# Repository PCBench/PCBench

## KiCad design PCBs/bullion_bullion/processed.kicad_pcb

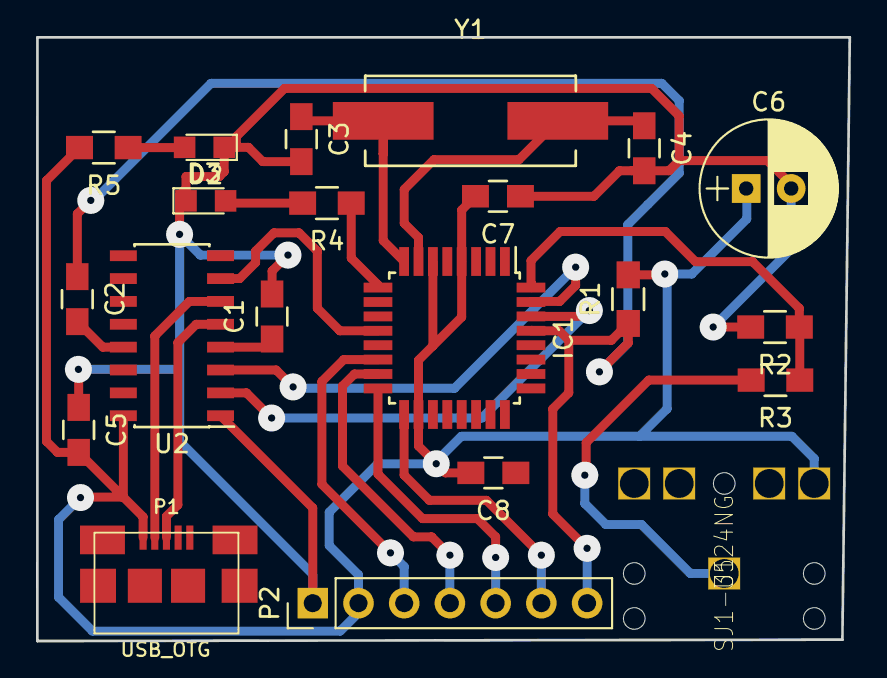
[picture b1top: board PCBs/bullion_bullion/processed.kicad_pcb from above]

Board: 2 copper layers, 45.1 x 33.5 mm, 21 parts (0 on the bottom side), 21 nets.

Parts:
C1, C2, C5, C7, C8: 0.1u; C_0805_HandSoldering
C3, C4: 22p; C_0805_HandSoldering
C6: 47u; CP_Radial_D7.5mm_P2.50mm
D2: BLUE; LED_0805
D3: RED; LED_0805
IC1: ATMEGA328P-A; TQFP-32_7x7mm_Pitch0.8mm
P1: USB_OTG; MICRO-B_USB
P2: CONN_01X07; Pin_Header_Straight_1x07_Pitch2.54mm
R1: 10k; R_0805_HandSoldering
R2: 2.2k; R_0805_HandSoldering
R3: 220; R_0805_HandSoldering
R4: 82; R_0805_HandSoldering
R5: 4.7k; R_0805_HandSoldering
U1: SJ1-3524NG; PIN-4
U2: CH340G; SOIC-16_3.9x9.9mm_Pitch1.27mm
Y1: Crystal; Crystal_HC49-SD_SMD

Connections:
+5V: C5.2, C6.1, C7.2, C8.2, IC1.4, IC1.6, IC1.18, P1.1, P2.2, R1.2, R5.2, U1.2, U2.16
CLKOUT: IC1.12, U2.7
DTR: C2.2, U2.13
GND: C1.2, C3.2, C4.2, C5.1, C6.2, C7.1, D2.1, D3.1, P2.1, R2.2, U2.1
MM_TXD: IC1.32, R2.1, R3.1
unnamed: C1.1, U2.4
unnamed: C2.1, IC1.29, P2.7, R1.1
unnamed: C3.1, IC1.8, Y1.1
unnamed: C4.1, IC1.7, Y1.2
unnamed: D2.2, R4.2
unnamed: D3.2, R5.1
unnamed: IC1.9, R4.1
unnamed: IC1.14, P2.3
unnamed: IC1.15, P2.4
unnamed: IC1.16, P2.5
unnamed: IC1.17, P2.6
unnamed: P1.2, U2.6
unnamed: P1.3, U2.5
unnamed: R3.2, U1.1
RXD: IC1.30, U2.2
TXD: IC1.31, U2.3

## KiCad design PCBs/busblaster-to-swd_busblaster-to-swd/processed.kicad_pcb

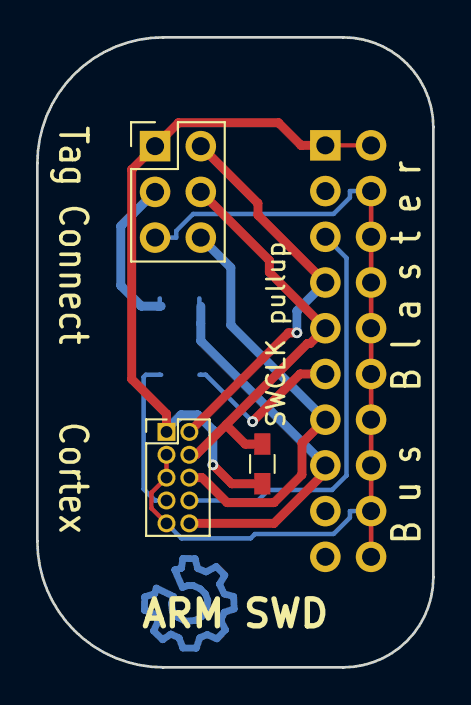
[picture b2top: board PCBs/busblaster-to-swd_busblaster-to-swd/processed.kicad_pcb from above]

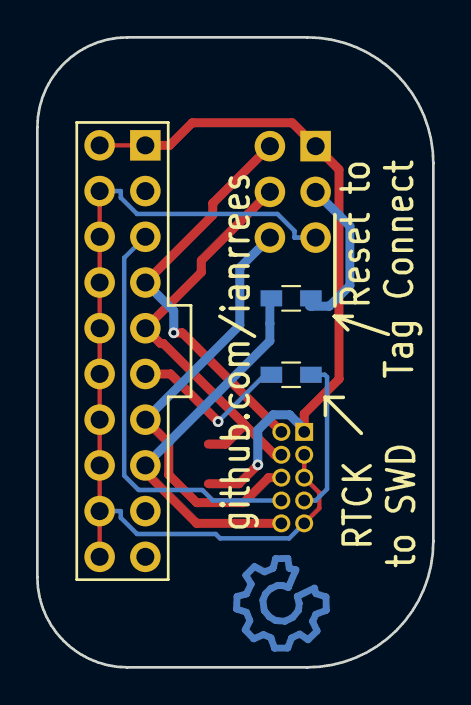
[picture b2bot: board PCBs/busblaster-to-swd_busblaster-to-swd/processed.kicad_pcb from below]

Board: 2 copper layers, 22.0 x 35.0 mm, 6 parts (2 on the bottom side), 10 nets.

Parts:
J101: CONN_02X10; Pin_Header_Straight_2x10_Pitch2.54mm
J102: Tag Connect; Pin_Header_Straight_2x03_Pitch2.54mm
J103: CONN_02X05; Pin_Header_Straight_2x05_Pitch1.27mm
JP101, JP102: Jumper_NC_Small; R_0603_HandSoldering
R101: 1k; R_0603_HandSoldering

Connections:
/GND: J101.4, J101.6, J101.8, J101.10, J101.12, J101.14, J101.16, J101.18, J101.20, J102.5, J103.3, J103.5, J103.9
/RTCK: J103.7, JP102.2
/SWO/TDO: J101.13, J102.6, J103.6
/TCK/SWCLK: J101.9, J102.4, J103.4, R101.2
/TDI: J101.5, J103.8
/TMS/SWDIO: J101.7, J102.2, J103.2
/Vtarget: J101.1, J101.2, J102.1, J103.1, R101.1
/~Reset: J102.3, JP101.1
unnamed: J101.11, JP102.1
unnamed: J101.15, J103.10, JP101.2

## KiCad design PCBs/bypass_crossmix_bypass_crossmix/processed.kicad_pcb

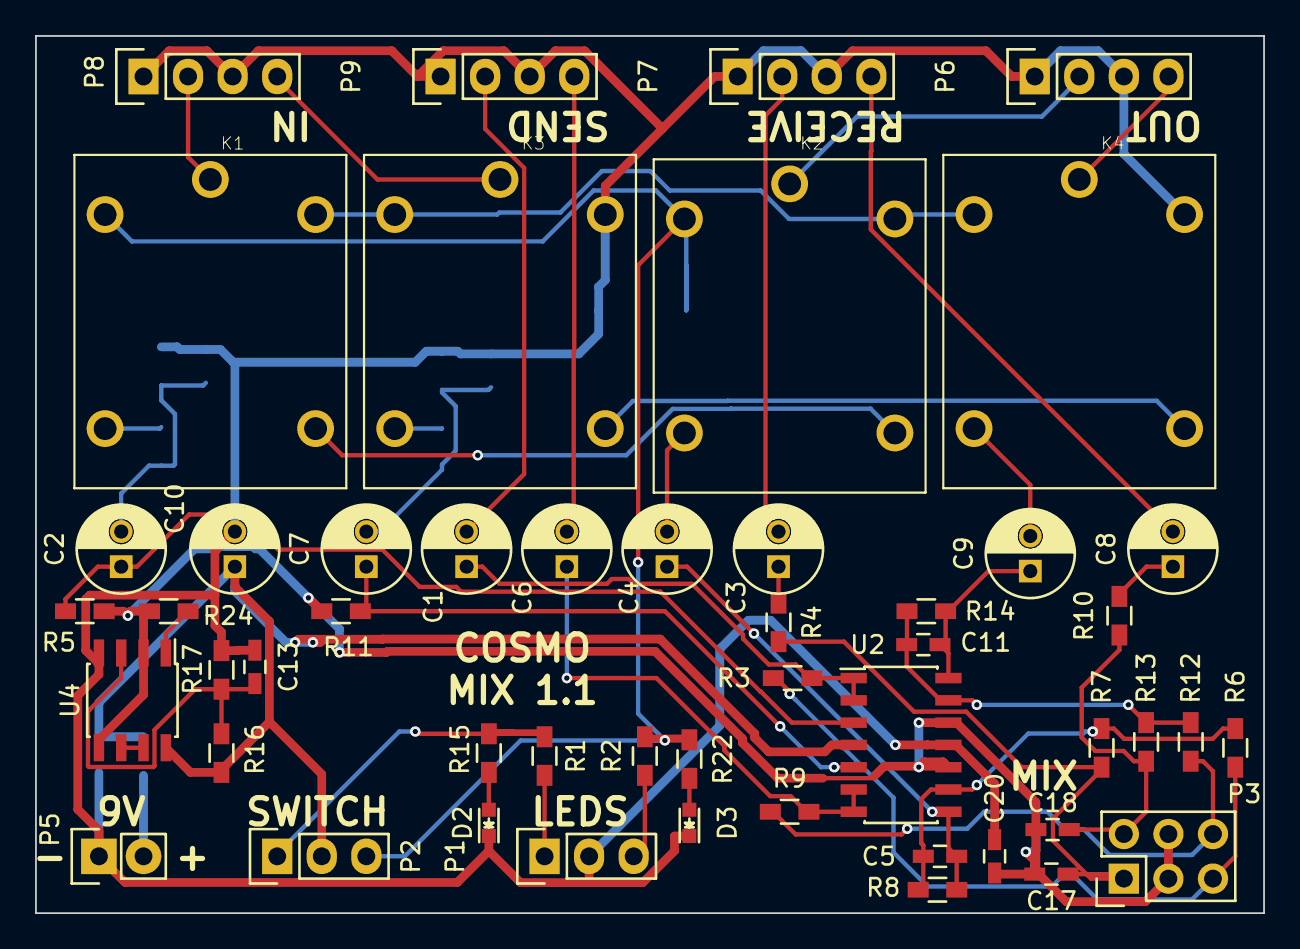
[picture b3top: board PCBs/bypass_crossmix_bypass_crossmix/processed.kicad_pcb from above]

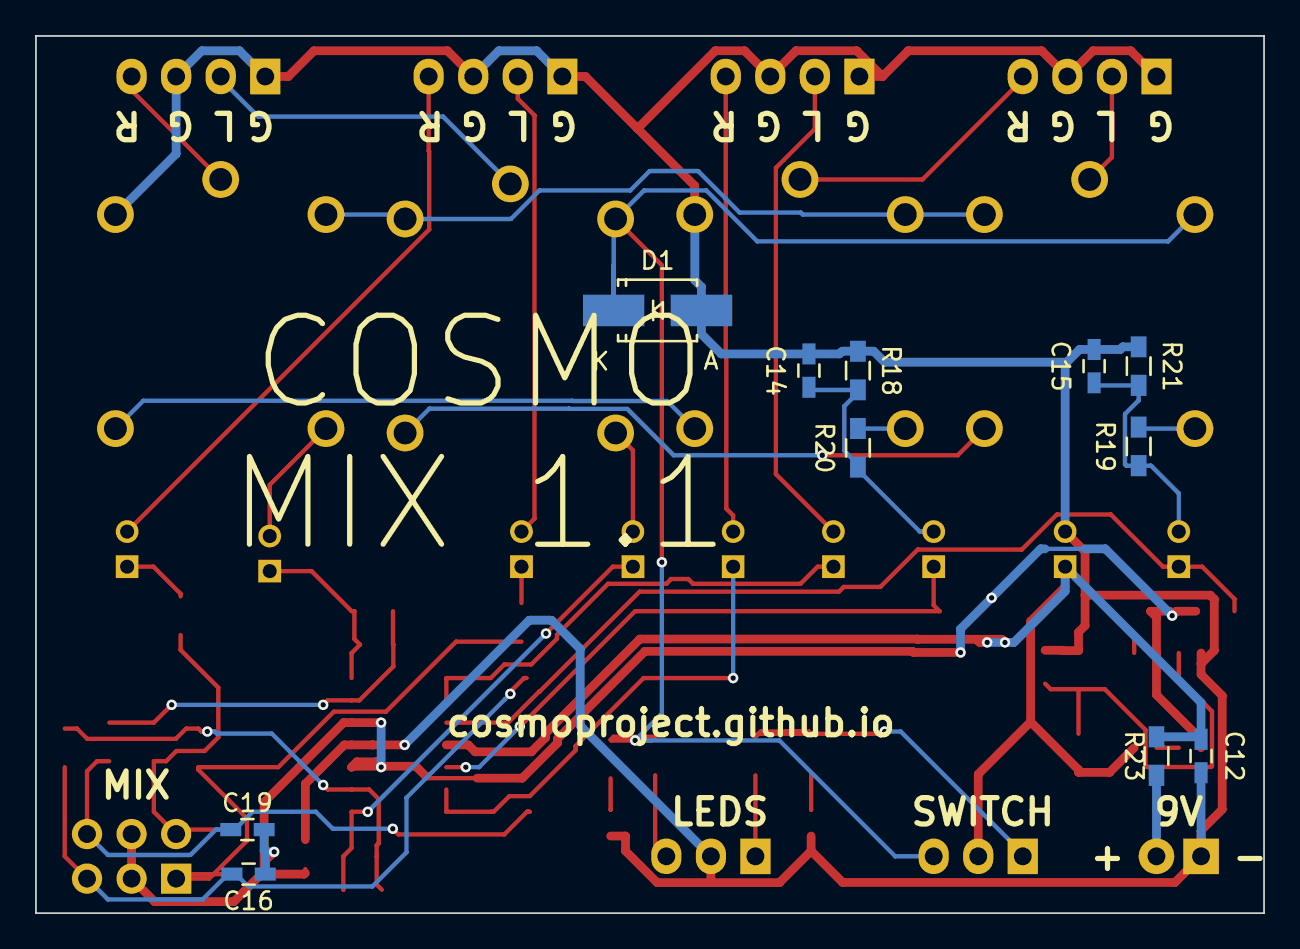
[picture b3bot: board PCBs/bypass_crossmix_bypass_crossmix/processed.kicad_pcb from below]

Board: 2 copper layers, 70.0 x 50.0 mm, 61 parts (11 on the bottom side), 44 nets.

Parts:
C1, C2, C3, C4, C6, C7, C8, C9, C10: 100u; C_Radial_D5_L11_P2
C5, C11: C; C_0603_HandSoldering
C12, C13, C20: 100n; C_0603_HandSoldering
C14, C15: 10n; C_0603_HandSoldering
C16, C17, C18, C19: 100p; C_0603_HandSoldering
D1: D; SMA_Handsoldering
D2: RED; LED-0603
D3: GREEN; LED-0603
K1, K2, K3, K4: RELAY-HLS8L-DC5V-S-C(5P-19X15MM); REY5-19.0X15.0X15.0MM
P1: STATUS LED; Pin_Header_Straight_1x03
P2: SWITCH; Pin_Header_Straight_1x03
P3: DRYWET; Pin_Header_Straight_2x03
P5: 9V; Pin_Header_Straight_1x02
P6: OUT; Pin_Header_Straight_1x04
P7: RECEIVE; Pin_Header_Straight_1x04
P8: IN; Pin_Header_Straight_1x04
P9: SEND; Pin_Header_Straight_1x04
R1, R15: 180; R_0603_HandSoldering
R2, R22: 150; R_0603_HandSoldering
R3, R4, R6, R7, R9, R10, R12, R13, R16, R17: 47k; R_0603_HandSoldering
R5, R11, R18, R21: 1M; R_0603_HandSoldering
R8, R14: 100k; R_0603_HandSoldering
R19, R20: 470; R_0603_HandSoldering
R23, R24: 12; R_0603_HandSoldering
U2: TL074; SOIC-14_3.9x8.7mm_Pitch1.27mm
U4: LM358; SOIC-8_3.9x4.9mm_Pitch1.27mm

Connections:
+5V: C10.1, C12.1, P2.2, R16.1, R23.1, U2.4, U4.8
-5V: C10.2, C12.2, C13.1, C14.2, C15.2, C20.2, D1.2, D2.1, D3.1, K3.3, K4.3, P1.2, P5.1, P6.1, P6.3, P7.1, P7.3, P8.1, P8.3, P9.1, P9.3, R17.2, R18.1, R21.1, U2.11, U4.4
/in_left: K1.1, P8.2
/in_right: K3.1, P8.4
/out_left: K2.1, P6.2
/out_right: K4.1, P6.4
/receive_left: C3.2, P7.2
/receive_right: C8.2, P7.4
/send_left: C1.2, P9.2
/send_right: C6.2, P9.4
GND: C16.1, C17.2, C18.2, C19.1, C20.1, P3.3, P3.4, R5.2, R11.2, R24.1, U2.10, U2.12, U4.2, U4.5
unnamed: C1.1, R3.2, U2.1, U2.2
unnamed: C2.1, R5.1, U2.3
unnamed: C3.1, R4.1
unnamed: C4.1, C5.2, R8.2, U2.8
unnamed: C4.2, K2.4
unnamed: C5.1, R6.1, R7.1, R8.1, U2.9
unnamed: C6.1, R9.2, U2.6, U2.7
unnamed: C7.1, R11.1, U2.5
unnamed: C8.1, R10.1
unnamed: C9.2, K4.4
unnamed: C11.1, R12.1, R13.1, R14.1, U2.13
unnamed: C9.1, C11.2, R14.2, U2.14
unnamed: C13.2, R16.2, R17.1, U4.3
unnamed: C7.2, C14.1, R18.2, R20.1
unnamed: C2.2, C15.1, R19.1, R21.2
unnamed: C16.2, P3.5, R3.1, R6.2
unnamed: C17.1, P3.1, R4.2, R7.2
unnamed: C18.1, P3.2, R10.2, R13.2
unnamed: C19.2, P3.6, R9.1, R12.2
unnamed: D1.1, K1.2, K2.2, P2.3, R2.2, R22.1
unnamed: D2.2, R15.1
unnamed: D3.2, R22.2
unnamed: K1.3, K2.3, K3.2, K4.2
unnamed: K1.4, R19.2
unnamed: K1.5, K2.5
unnamed: K3.4, R20.2
unnamed: K3.5, K4.5
unnamed: P1.1, R1.1
unnamed: P1.3, R2.1
unnamed: P2.1, R1.2, R15.2
unnamed: P5.2, R23.2
unnamed: R24.2, U4.1
unnamed: U4.6, U4.7

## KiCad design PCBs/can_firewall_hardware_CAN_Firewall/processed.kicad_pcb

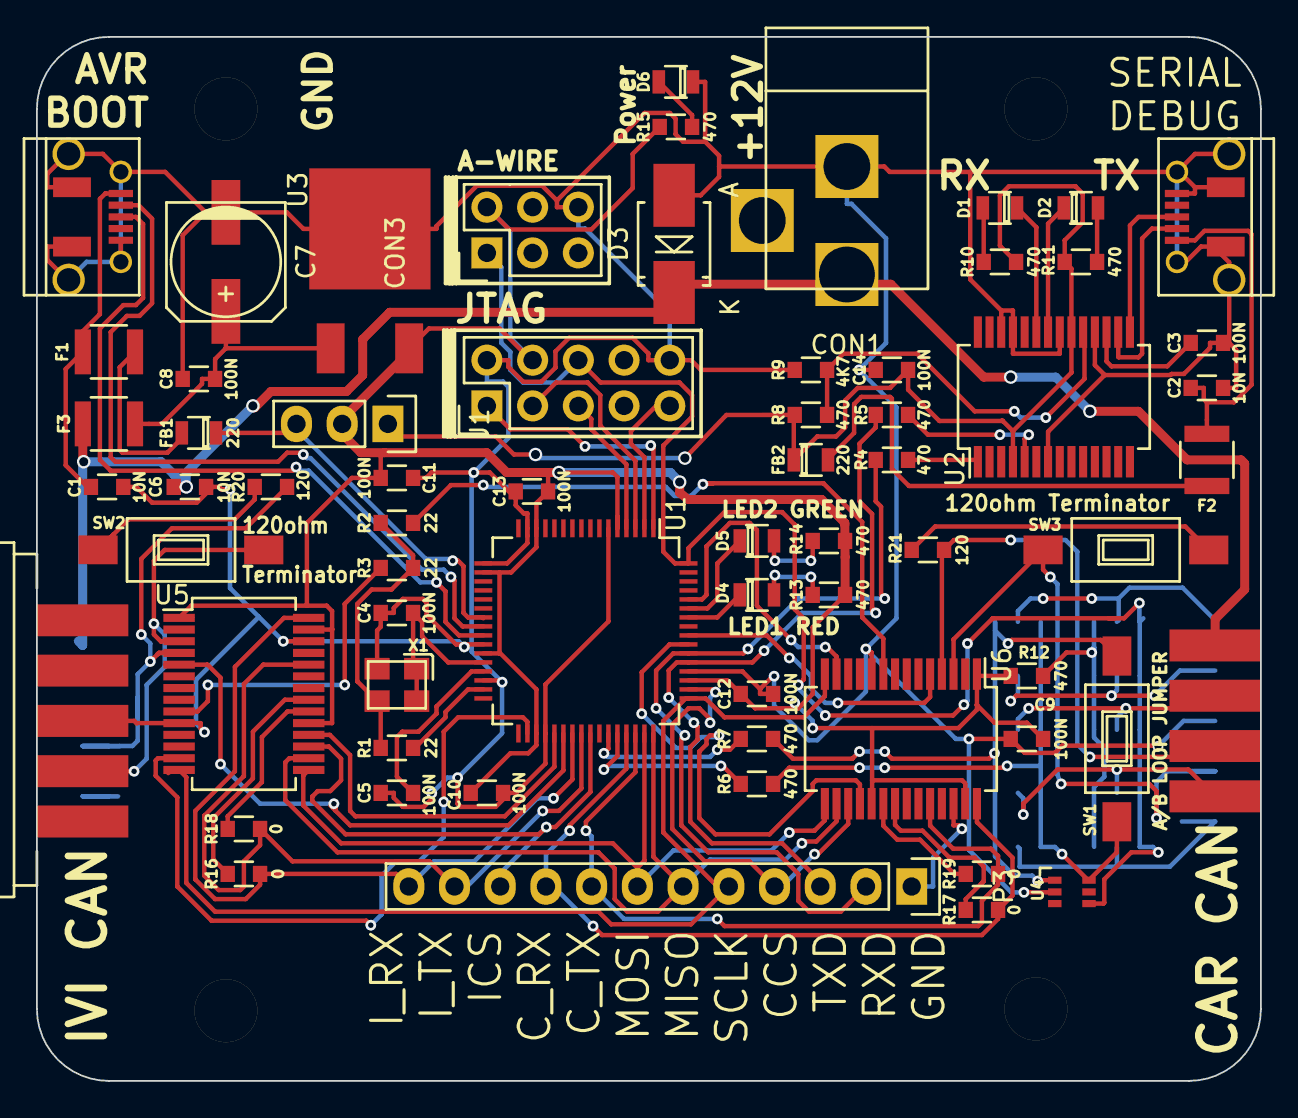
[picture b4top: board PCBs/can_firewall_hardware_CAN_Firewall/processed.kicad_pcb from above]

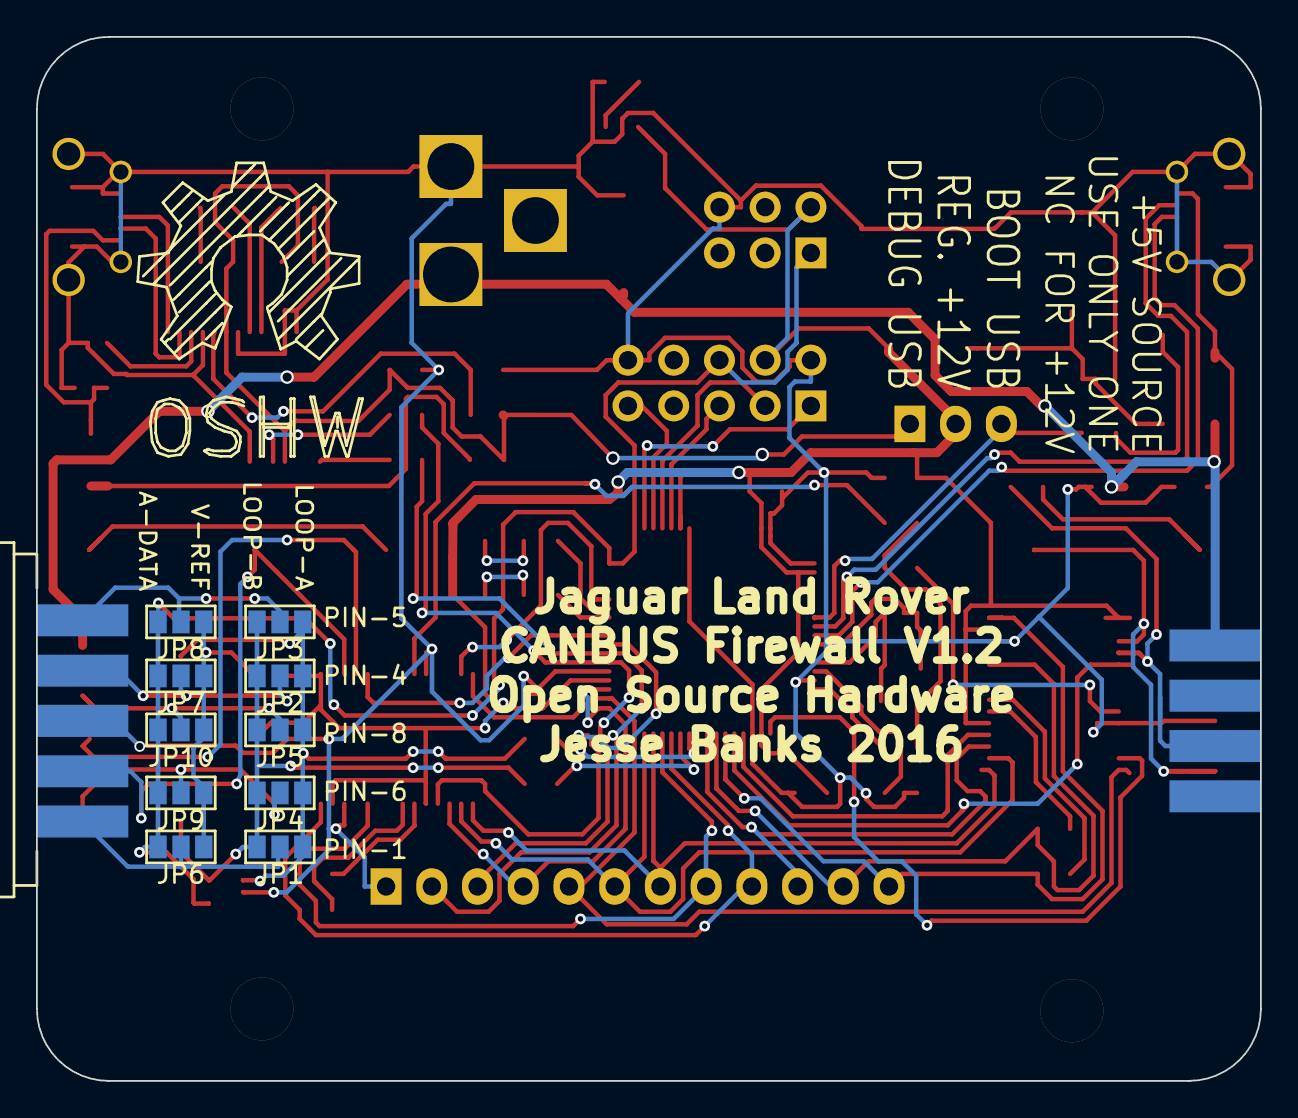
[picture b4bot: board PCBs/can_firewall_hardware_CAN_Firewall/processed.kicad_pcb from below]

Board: 2 copper layers, 68.0 x 58.0 mm, 75 parts (11 on the bottom side), 75 nets.

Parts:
C1, C2, C6: 10N; R_0603_sm
C3, C4, C5, C8, C9, C10, C11, C12, C13, C14: 100N; R_0603_sm
C7: 47U; c_elec_6.3x5.3
CON1: BARREL_JACK
CON2: AVR-JTAG-10; Pin_Header_Straight_2x05
CON3: AVR-AW-6; Pin_Header_Straight_2x03
D1: YELLOW; Diode_0805_12
D2: WHITE; Diode_0805_12
D3: SMBJ16A; SMB_Handsoldering
D4: RED; Diode_0805_12
D5: GREEN; Diode_0805_12
D6: BLUE; Diode_0805_12
F1, F2, F3: FUSE; R_1210_SM
FB1, FB2: 220; Diode_0805_12_SM
J1: +5V_SRC; Pin_Header_Straight_1x03
J2, J3: DB9; DB9F_CI
JP1, JP6: Matrix A; GS3
JP2, JP7: Matrix B; GS3
JP3, JP8: Matrix C; GS3
JP4, JP9: Matrix D; GS3
JP5, JP10: Matrix E; GS3
P1, P2: USB_OTG; USB_Micro-B-DX4R005JJ2R1800
P3: DIAG Port; Pin_Header_Straight_1x12
R1, R2, R3: 22; R_0603_sm
R4, R5, R6, R7, R8, R10, R11, R12, R13, R14, R15: 470; R_0603_sm
R9: 4K7; R_0603_sm
R16, R17, R18, R19: 0; R_0603_sm
R20, R21: 120; R_0603_sm
SW1, SW2, SW3: SPST; SW_SPST_FSMSM_SM
U1: AT32UC3C; LQFP-64_10x10mm_Pitch0.5mm
U2: FT232RL-SSOP; SSOP-28_5.3x10.2mm_Pitch0.65mm
U3: MC78M05CDT; D-Pak_TO252AA
U4: SMF05; SC-70-6
U5, U6: MCP25625; SSOP-28_5.3x10.2mm_Pitch0.65mm
X1: TXC

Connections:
+3V3: C4.1, U1.28, X1.1, X1.4
+5V: C9.1, C10.1, C11.1, C12.1, C13.1, CON2.4, CON3.2, J1.2, R12.2, R13.2, R14.2, R15.2, U1.5, U1.14, U1.18, U1.27, U1.35, U1.51, U3.3, U5.1, U5.19, U5.27, U6.1, U6.19, U6.27
+12V: C6.1, CON1.1, D3.1, F3.1, J2.9, J3.9
A: J3.1, JP1.2, JP6.2
B: J3.4, JP2.2, JP7.2
C: J3.5, JP3.2, JP8.2
CAR_CANH: J3.7, R21.2, U6.4
CAR_CANL: J3.2, SW3.2, U6.3
CAR_CS: P3.4, U1.50, U6.17
CAR_INT: U1.60, U6.13
CAR_RESET: U1.55, U6.18
CAR_RxCAN: P3.9, R17.1, U1.45, U6.28
CAR_STBY: U1.56, U6.5
CAR_TxCAN: P3.8, R19.1, U1.46, U6.24
CLK1: R1.1, U1.31
CLK2: R2.1, U6.9
CLK3: R3.1, U5.9
D: J3.6, JP4.2, JP9.2
E: J3.8, JP5.2, JP10.2
GND: C1.2, C2.2, C3.2, C4.2, C5.2, C6.2, C7.2, C8.2, C9.2, C10.2, C11.2, C12.2, C13.2, C14.2, CON1.2, CON2.2, CON2.10, CON3.6, D3.2, D6.1, J2.3, J3.3, P1.5, P1.6, P2.5, P2.6, P3.1, R9.2, U1.6, U1.15, U1.17, U1.26, U1.30, U1.36, U1.52, U2.7, U2.18, U2.21, U2.25, U2.26, U3.4, U4.2, U5.10, U5.26, U6.10, U6.26, X1.2
IVI_CANH: J2.7, R20.2, U5.4
IVI_CANL: J2.2, SW2.2, U5.3
IVI_CS: P3.10, U1.41, U5.17
IVI_INT: U1.34, U5.13
IVI_RESET: U1.37, U5.18
IVI_RxCAN: P3.12, R16.1, U1.39, U5.28
IVI_STBY: U1.38, U5.5
IVI_TxCAN: P3.11, R18.1, U1.40, U5.24
LED1: D4.1, U1.58
LED2: D5.1, U1.59
LOOP_A: JP1.1, JP2.1, JP3.1, JP4.1, JP5.1, R7.1, SW1.2, U4.1
LOOP_B: JP1.3, JP2.3, JP3.3, JP4.3, JP5.3, R6.1, SW1.1, U4.6
MISO: P3.6, U1.48, U5.16, U6.16
MOSI: P3.7, U1.47, U5.15, U6.15
unnamed: C1.1, F1.2, P1.1
unnamed: C2.1, F2.2, P2.1
unnamed: C3.1, U2.17
unnamed: C5.1, U1.29
unnamed: C7.1, C8.1, F3.2, U3.1
unnamed: D1.1, U2.23
unnamed: D1.2, R10.1
unnamed: D2.1, U2.22
unnamed: D2.2, R11.1
unnamed: D4.2, R13.1
unnamed: D5.2, R14.1
unnamed: D6.2, R15.1
unnamed: F1.1, FB1.2
unnamed: F2.1, FB2.2
unnamed: JP6.1, JP7.1, JP8.1, JP9.1, JP10.1, R12.1
unnamed: R1.2, R2.2, R3.2, X1.3
unnamed: R4.2, U2.1
unnamed: R5.2, U2.5
unnamed: R6.2, U1.44
unnamed: R7.2, U1.43
unnamed: R8.1, R9.1, U2.19
unnamed: R16.2, U5.21
unnamed: R17.2, U6.21
unnamed: R18.2, U5.20
unnamed: R19.2, U6.20
unnamed: R20.1, SW2.1
unnamed: R21.1, SW3.1
RX_DBG: P3.2, R4.1, U1.54
SCLK: P3.5, U1.49, U5.14, U6.14
TCK: CON2.1, U1.1
TDI: CON2.9, U1.2
TDO: CON2.3, U1.3
TMS: CON2.5, U1.4
TX_DBG: P3.3, R5.1, U1.53
USB5: C14.1, FB2.1, J1.1, R8.2, R10.2, R11.2, U2.4, U2.20
USB+: P2.3, U2.15
USB-: P2.2, U2.16
USBM: P1.2, U1.24
USBP: P1.3, U1.25
VBUS: FB1.1, J1.3, U1.23
~RESET/A_DATA: CON2.6, CON3.1, JP6.3, JP7.3, JP8.3, JP9.3, JP10.3, U1.64, U4.4

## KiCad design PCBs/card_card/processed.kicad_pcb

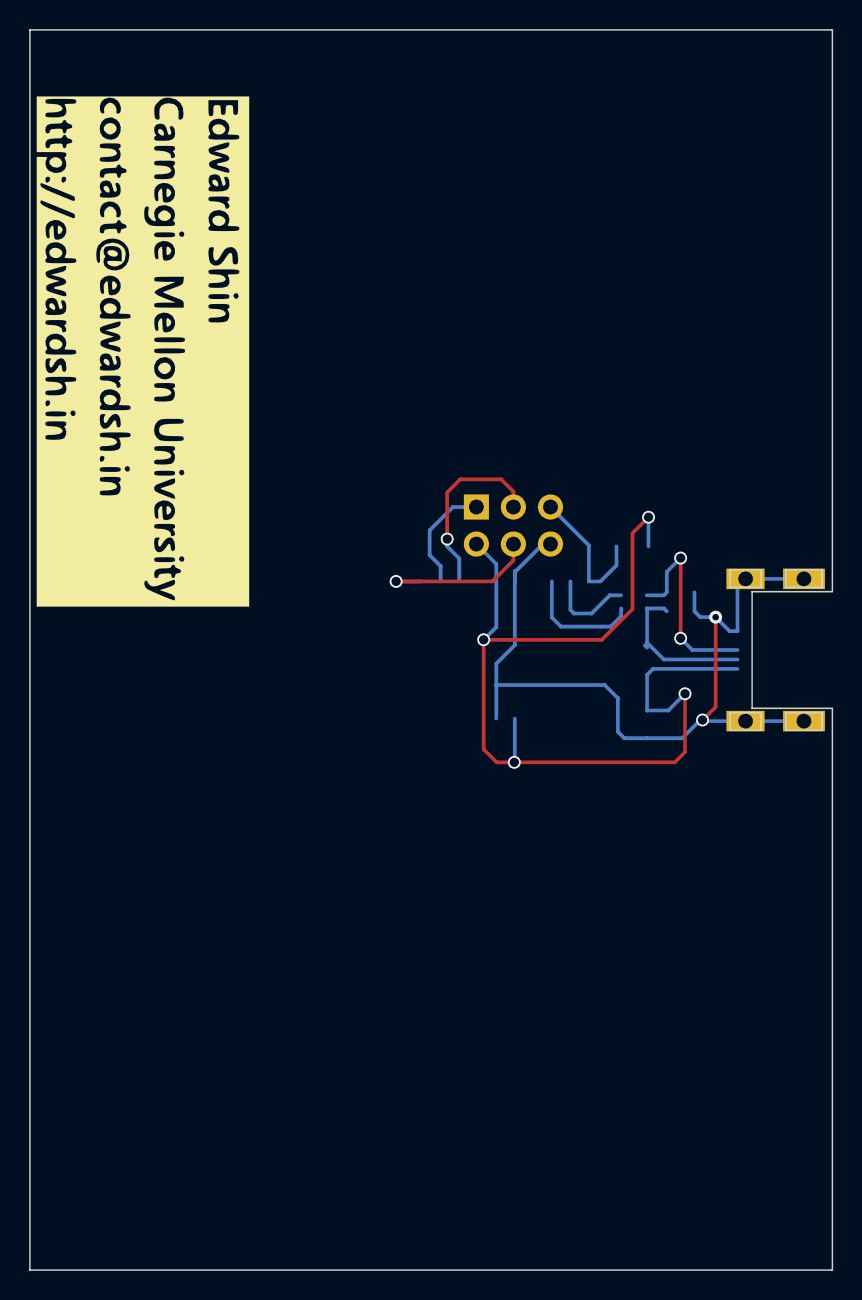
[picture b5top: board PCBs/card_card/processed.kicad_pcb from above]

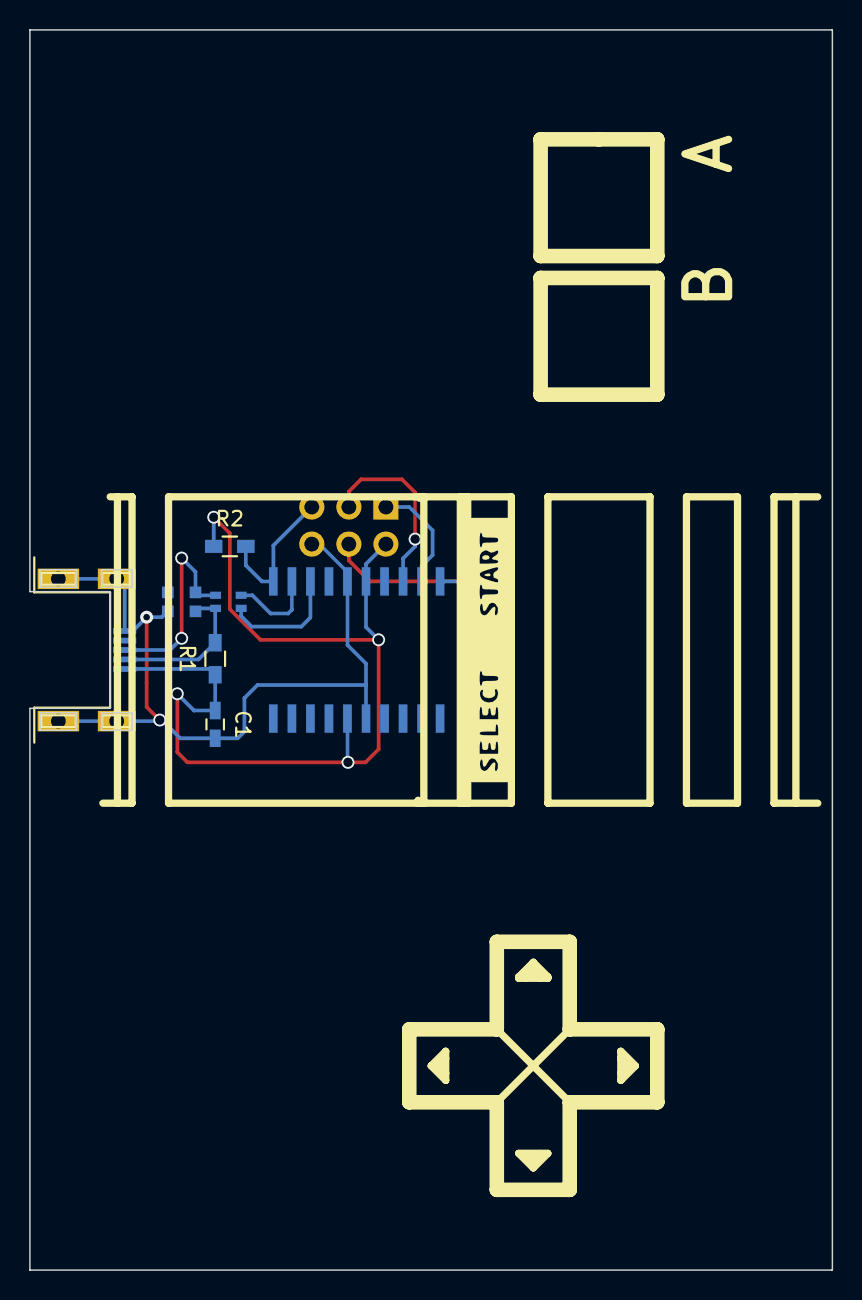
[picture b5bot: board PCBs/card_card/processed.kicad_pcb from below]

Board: 2 copper layers, 55.0 x 85.0 mm, 8 parts (8 on the bottom side), 10 nets.

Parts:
C1: 0.1uF; C_0603_HandSoldering
CON1: USB-MINI-B; 15542661MicroUSBB
D1: ZENERARRAY; SMini4-F3-B
IC1: ATTINY26-S; SOIC-20_7.5x12.8mm_Pitch1.27mm
P1: CONN_3X2; Pin_Header_Straight_2x03
R1: 1.5k; R_0603_HandSoldering
R2: 4.7k; R_0603_HandSoldering
RP1: 68R; MNR12

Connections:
+5V: C1.1, CON1.1, IC1.5, IC1.15, P1.2, R1.1, R2.1
/MISO: IC1.2, P1.1
/MOSI: IC1.1, P1.4
/RST: IC1.10, P1.5, R2.2
/SCK: IC1.3, P1.3
GND: C1.2, CON1.5, CON1.6, CON1.7, CON1.8, CON1.9, D1.1, D1.2, IC1.6, IC1.16, P1.6
unnamed: CON1.2, D1.3, R1.2, RP1.4
unnamed: CON1.3, D1.4, RP1.3
unnamed: IC1.8, RP1.1
unnamed: IC1.9, RP1.2

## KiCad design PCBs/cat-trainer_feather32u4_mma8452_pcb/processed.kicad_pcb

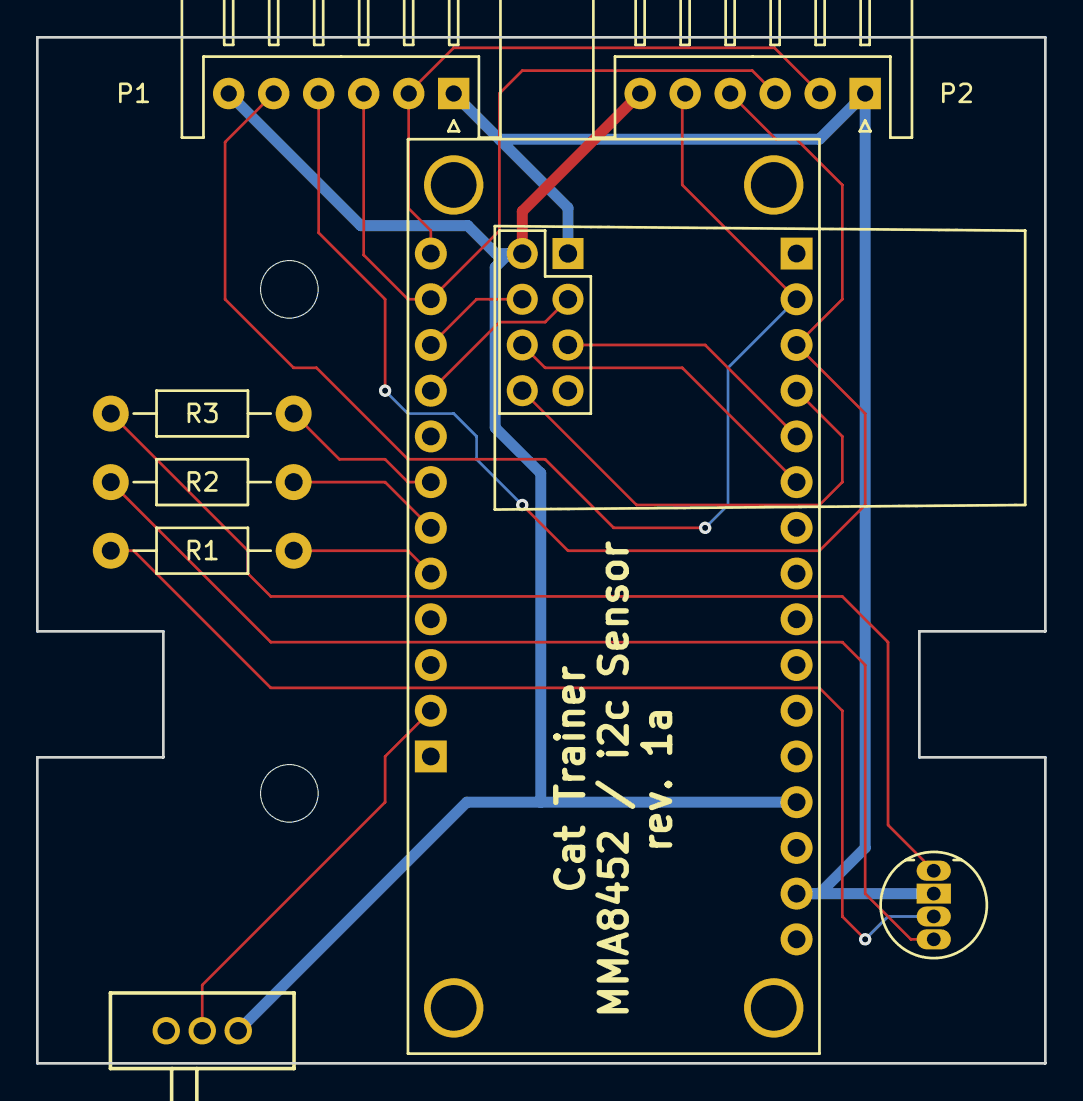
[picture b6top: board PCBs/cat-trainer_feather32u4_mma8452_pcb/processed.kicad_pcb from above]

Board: 2 copper layers, 56.0 x 57.0 mm, 9 parts (0 on the bottom side), 18 nets.

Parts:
D1: LED_RBG; LED-RGB-5MM_Common_Cathode
P1, P2: CONN_01X06; JST_XH_S06B-XH-A_06x2.50mm_Angled
R1, R2, R3: R; Resistor_Horizontal_RM10mm
SW1: SPST; DPST_TE_SSJ12R04
U1: nRF24L01+; Socket_nRF24L01
U2: ADAFRUIT_FEATHER

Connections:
3V3: D1.2, P1.1, P2.1, U1.2, U2.15
CE: U1.3, U2.26
CSN: U1.4, U2.25
GND: P1.6, P2.6, SW1.1, U1.1, U2.13
unnamed: D1.1, R3.2
unnamed: D1.3, R1.2
unnamed: D1.4, R2.2
unnamed: P1.2, P2.2, U2.28
unnamed: P1.3, P2.3, U2.27
unnamed: P1.4, P2.4, U2.3
unnamed: P1.5, P2.5, U2.2
unnamed: R1.1, U2.21
unnamed: R2.1, U2.22
unnamed: R3.1, U2.23
unnamed: SW1.2, U2.18
unnamed: U1.5, U2.6
unnamed: U1.6, U2.5
unnamed: U1.7, U2.4
